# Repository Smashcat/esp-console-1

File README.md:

# esp-console-1
Little hand-held ESP8266 based console with 240x320 LCD display, SDCard storage, 8 buttons and 2 sounders :) This includes an on-board programming circuit and USB serial port, so that it can be programmed easily using Arduino! Estimate around $12 in parts, including PCB, depending on PCB service and amount ordered - I used JLCPCB to buy 10.

I have recently received the PCBs back from JLCPCB for this design, and it works great!

Youtube video of older design here: https://www.youtube.com/watch?v=sWY_PZYmeA4

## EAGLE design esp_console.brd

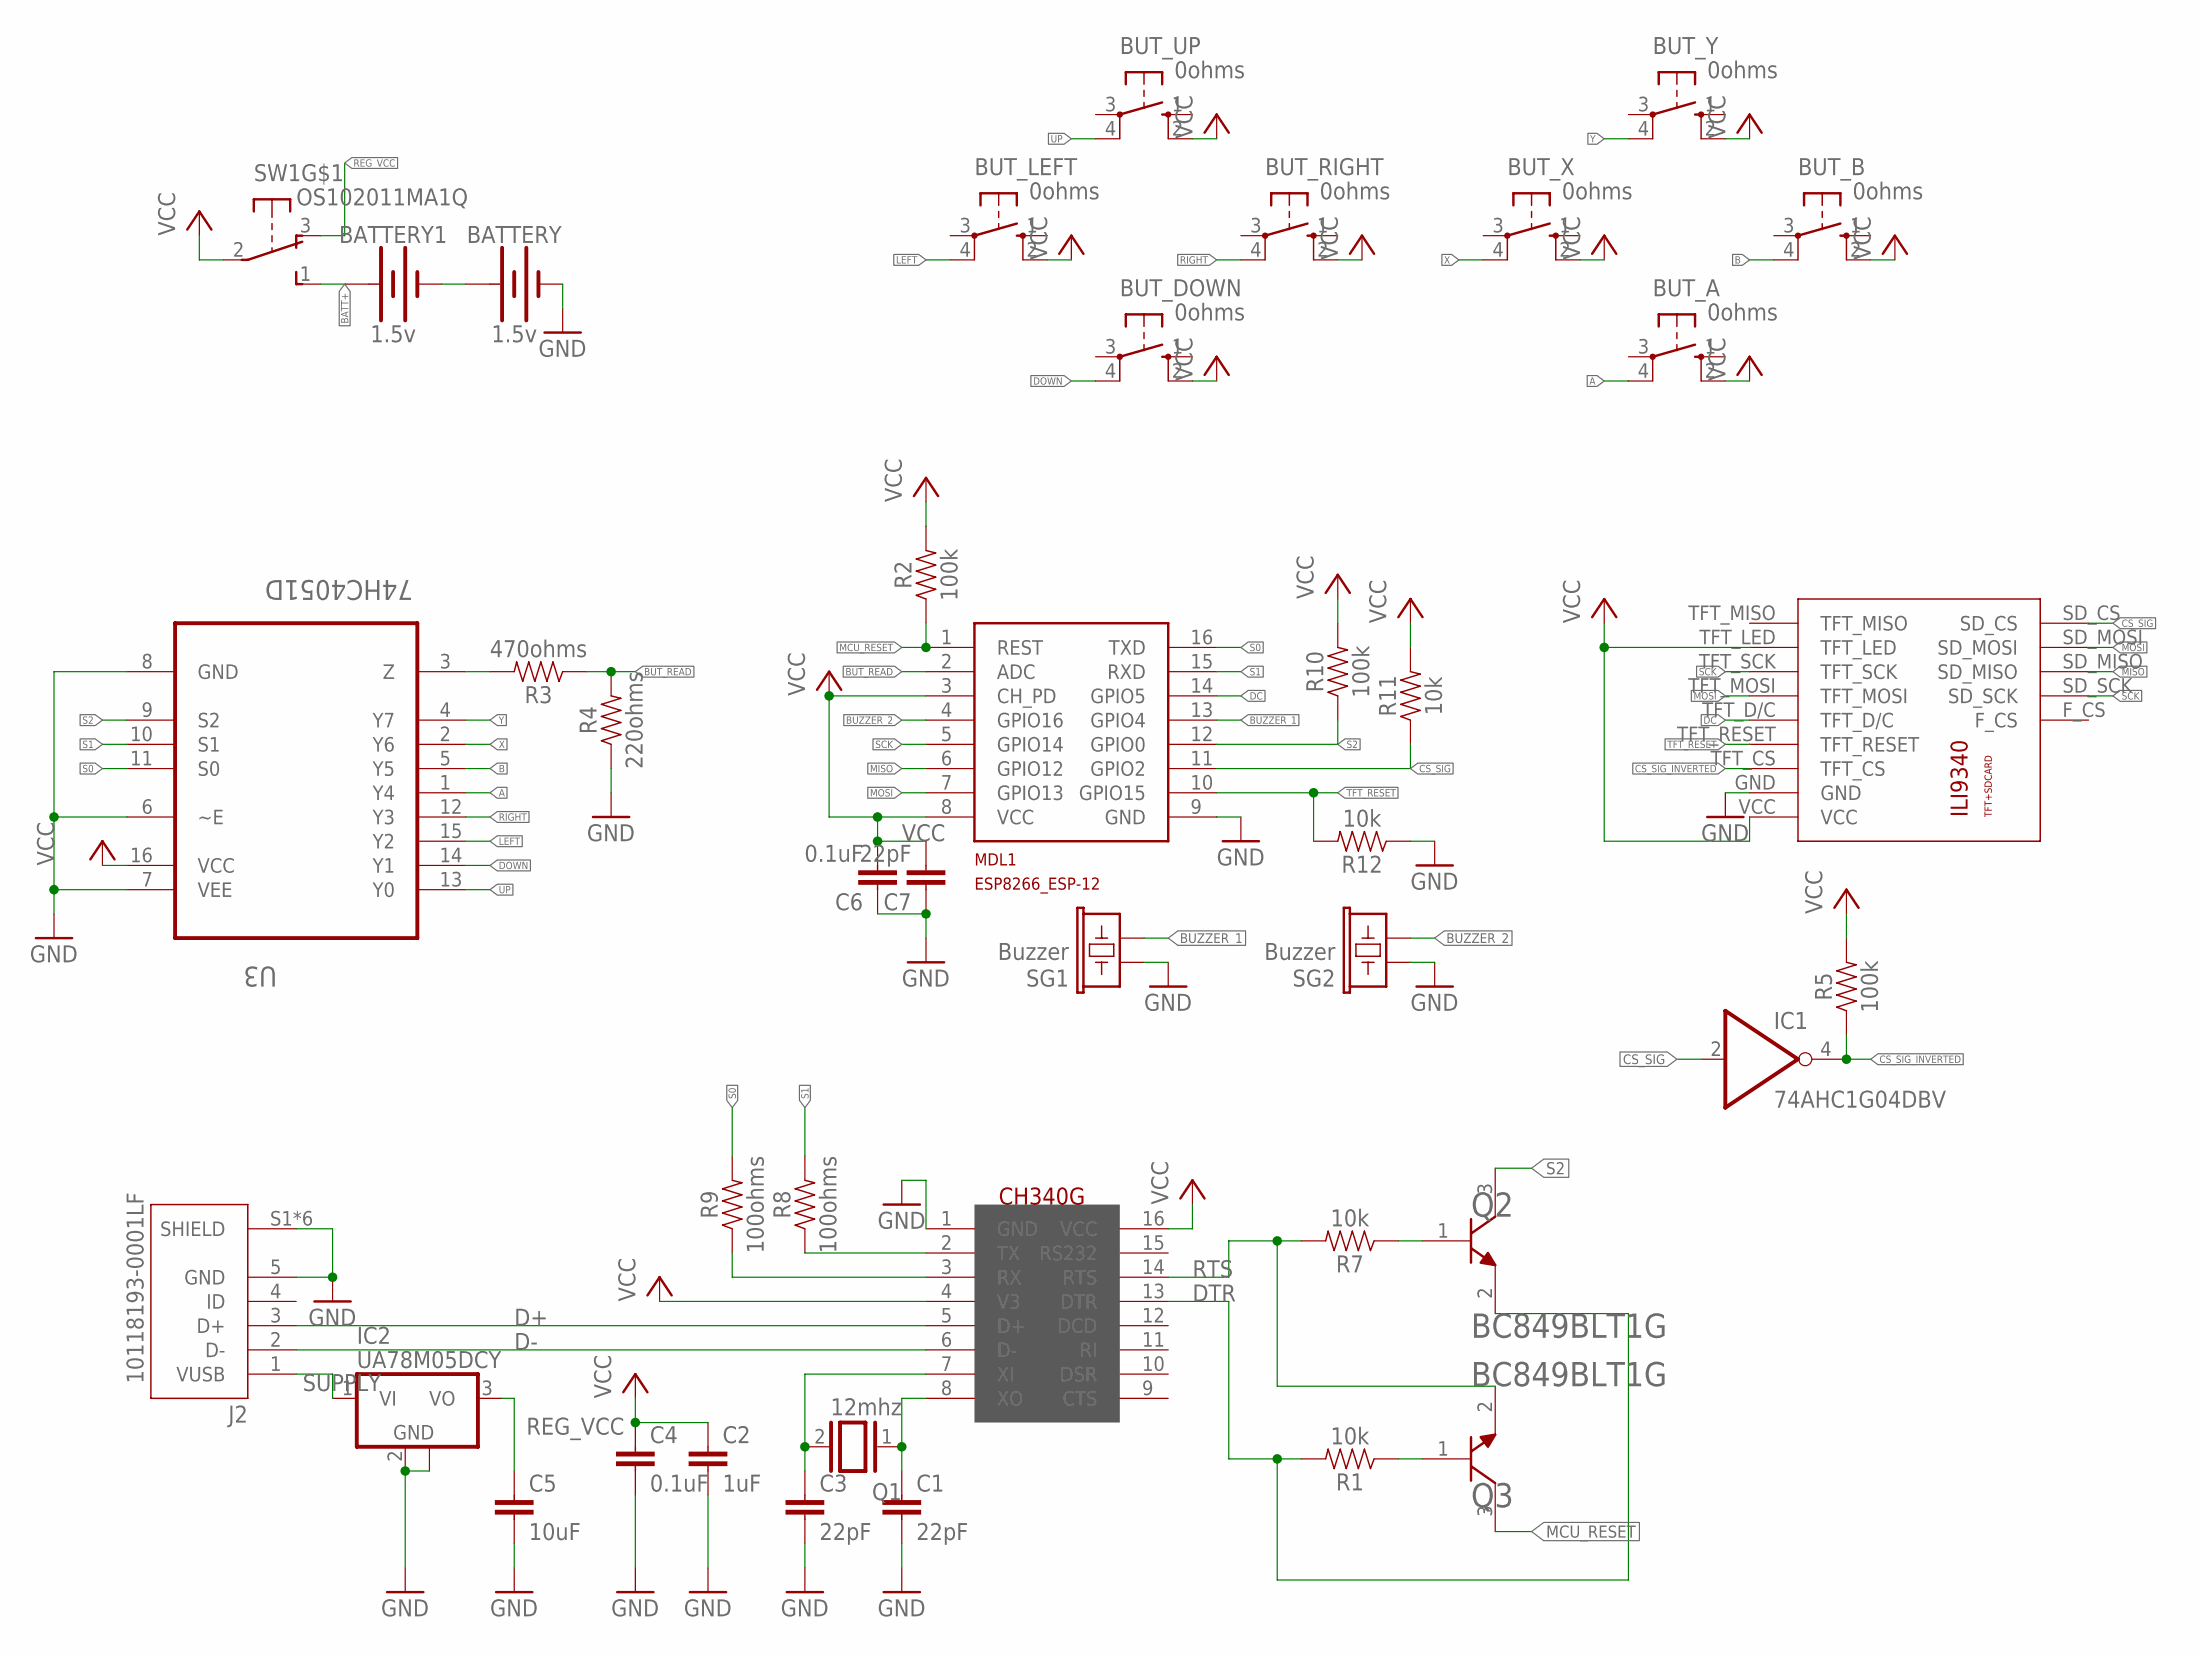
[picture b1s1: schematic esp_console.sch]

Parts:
BATTERY, BATTERY1: 1.5v; BATTERY-AA
BUT_A: 0ohms; B3F-10XX
BUT_B: 0ohms; B3F-10XX
BUT_DOWN: 0ohms; B3F-10XX
BUT_LEFT: 0ohms; B3F-10XX
BUT_RIGHT: 0ohms; B3F-10XX
BUT_UP: 0ohms; B3F-10XX
BUT_X: 0ohms; B3F-10XX
BUT_Y: 0ohms; B3F-10XX
C1, C3, C7: 22pF; C0603
C2: 1uF; C0603
C4, C6: 0.1uF; C0603
C5: 10uF; C0603
IC1: 74AHC1G04DBV; SOT23-5
IC2: UA78M05DCY; SOT223
J2: 10118193-0001LF; FCI_10118193-0001LF
MDL1: MCU; ESP8266-ESP12
Q1: 12mhz; QS
Q2, Q3: ON_SEMICONDUCTOR_BC849BLT1GON_SEMICONDUCTOR_BC849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; ON_SEMICONDUCTOR_BC849BLT1G_0
R1, R7, R11, R12: 10k; 0603
R2, R5, R10: 100k; 0603
R3: 470ohms; 0603
R4: 220ohms; 0603
R8, R9: 100ohms; 0603
SG1, SG2: Buzzer; BUZZER-CCV
SW1: OS102011MA1Q
U3: 74HC4051D; SOIC127P600X175-16N
U$1: CH340G; SOIC16
U$2: ILI9340-5PIN

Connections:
A: BUT_A.4 (P1), U3.1 (Y4)
B: BUT_B.4 (P1), U3.5 (Y5)
BATT+: BATTERY1.PWR@1 (+), SW1.1 (S)
BATT_LINK: BATTERY.PWR@1 (+), BATTERY1.GND@1 (-)
BUT_READ: MDL1.2 (ADC), R3.1, R4.2
BUT_READ_3V3: R3.2, U3.3 (Z)
BUZZER_1: MDL1.13 (GPIO4), SG1.- (2)
BUZZER_2: MDL1.4 (GPIO16), SG2.- (2)
CRYSTALIN: C3.1, Q1.2, U$1.7 (XI)
CRYSTALOUT: C1.1, Q1.1, U$1.8 (XO)
CS_SIG: IC1.2 (I), MDL1.11 (GPIO2), R11.1, U$2.SD_CS
CS_SIG_INVERTED: IC1.4 (O), R5.1, U$2.TFT_CS
D+: J2.3 (D+), U$1.5 (D+)
D-: J2.2 (D-), U$1.6 (D-)
DC: MDL1.14 (GPIO5), U$2.TFT_D/C
DOWN: BUT_DOWN.4 (P1), U3.14 (Y1)
DTR: Q2.2 (E), R1.2, U$1.13 (DTR)
GND: BATTERY.GND@1 (-), C1.2, C2.2, C3.2, C4.2, C5.2, C6.1, C7.1, IC1.3 (GND), IC2.2 (GND), IC2.4 (GND), J2.5 (GND), J2.S1 (SHIELD), J2.S2 (SHIELD), J2.S3 (SHIELD), J2.S4 (SHIELD), J2.S5 (SHIELD), J2.S6 (SHIELD), MDL1.9 (GND), R4.1, R12.1, SG1.+ (1), SG2.+ (1), U3.6 (~E), U3.7 (VEE), U3.8 (GND), U$1.1 (GND), U$2.GND
LEFT: BUT_LEFT.4 (P1), U3.15 (Y2)
MCU_RESET: MDL1.1 (REST), Q3.3 (C), R2.1
MISO: MDL1.6 (GPIO12), U$2.SD_MISO
MOSI: MDL1.7 (GPIO13), U$2.SD_MOSI, U$2.TFT_MOSI
unnamed: Q3.1 (B), R1.1
unnamed: Q2.1 (B), R7.1
REG_VCC: C5.1, IC2.3 (VO), SW1.3 (O)
RIGHT: BUT_RIGHT.4 (P1), U3.12 (Y3)
RTS: Q3.2 (E), R7.2, U$1.14 (RTS)
S0: MDL1.16 (TXD), R9.2, U3.11 (S0)
S1: MDL1.15 (RXD), R8.2, U3.10 (S1)
S2: MDL1.12 (GPIO0), Q2.3 (C), R10.1, U3.9 (S2)
SCK: MDL1.5 (GPIO14), U$2.SD_SCK, U$2.TFT_SCK
SUPPLY: IC2.1 (VI), J2.1 (VUSB)
TFT_RESET: MDL1.10 (GPIO15), R12.2, U$2.TFT_RESET
TXFROMMCU: R9.1, U$1.3 (RX)
TXFROMPROGRAMMER: R8.1, U$1.2 (TX)
UP: BUT_UP.4 (P1), U3.13 (Y0)
VCC: BUT_A.2 (S1), BUT_B.2 (S1), BUT_DOWN.2 (S1), BUT_LEFT.2 (S1), BUT_RIGHT.2 (S1), BUT_UP.2 (S1), BUT_X.2 (S1), BUT_Y.2 (S1), C2.1, C4.1, C6.2, C7.2, IC1.5 (VCC), MDL1.3 (CH_PD), MDL1.8 (VCC), R2.2, R5.2, R10.2, R11.2, SW1.2, U3.16 (VCC), U$1.4 (V3), U$1.16 (VCC), U$2.TFT_LED, U$2.VCC
X: BUT_X.4 (P1), U3.2 (Y6)
Y: BUT_Y.4 (P1), U3.4 (Y7)

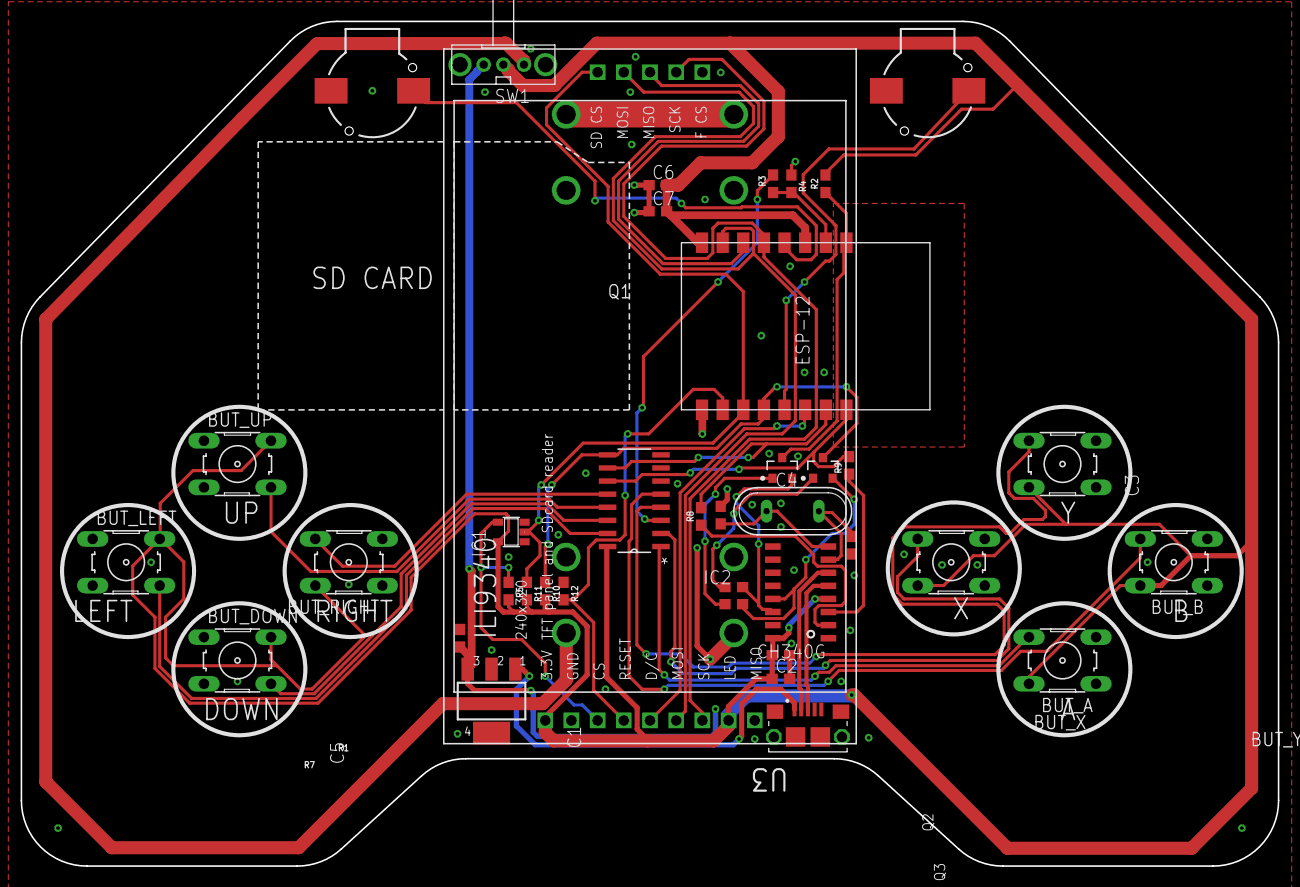
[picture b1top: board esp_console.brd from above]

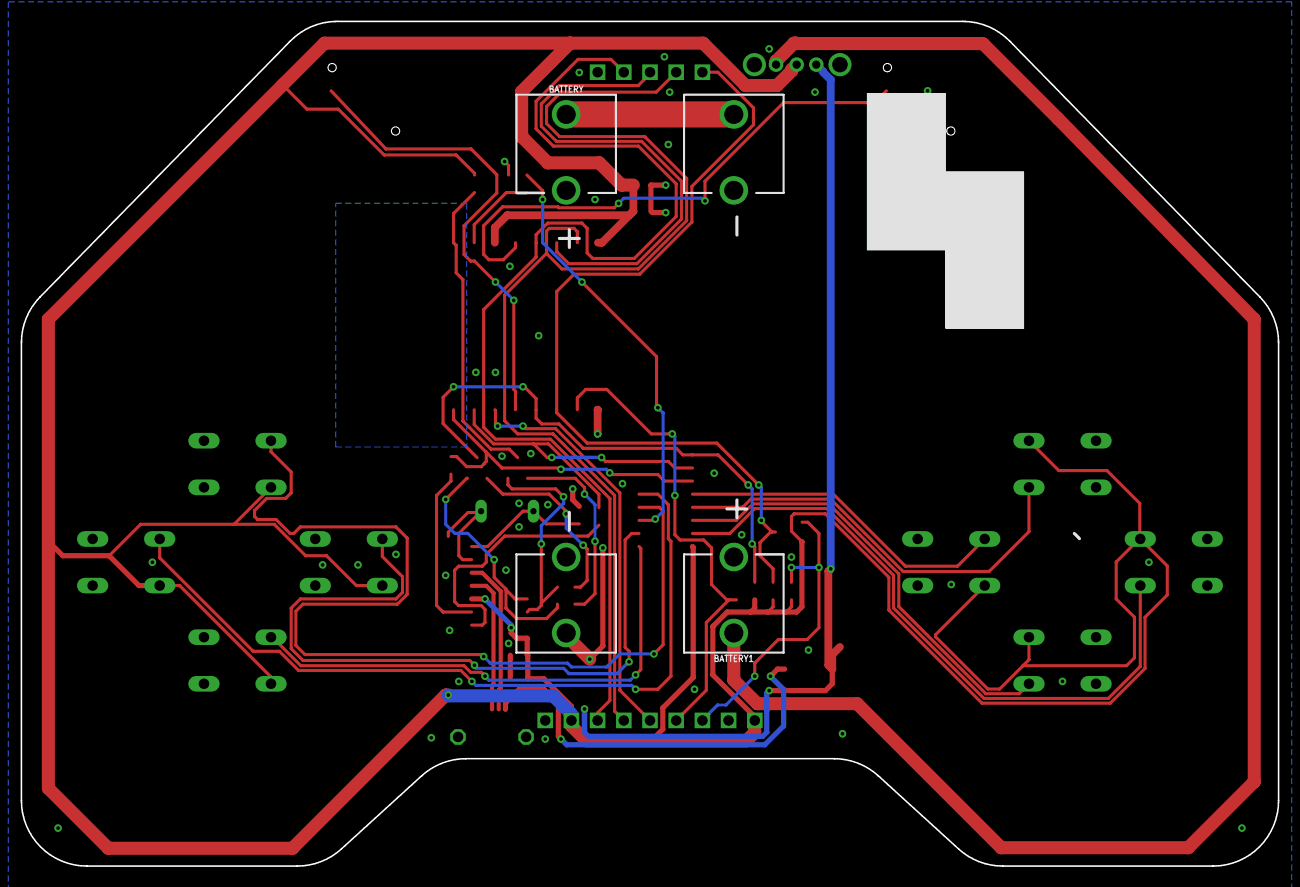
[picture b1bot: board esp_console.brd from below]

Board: 2 copper layers, 121.9 x 81.9 mm, 41 parts (2 on the bottom side), 39 nets.

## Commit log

2018-12-29 Added schematics
2018-12-29 Added lib for the USB port
2019-01-03 Updated design to 8 buttons
2019-01-03 New gerbers
2019-01-08 Added pullup to inverter, new gerbers
2019-01-08 Create LICENSE
2019-01-08 Update issue templates
2019-01-16 Added Tetris game and associated files
2019-01-16 Slight revision to wire routing, new gerbers

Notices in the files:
parts and their libraries:
SparkFun-Batteries: Licensing: Creative Commons ShareAlike 4.0 International - https://creativecommons.org/licenses/by-sa/4.0
